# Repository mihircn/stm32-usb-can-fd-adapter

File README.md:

# STM32 USB-to-CAN FD Adapter

A USB-to-CAN adapter designed in KiCad around the STM32G0B1CBT6. It connects to a PC over USB and interfaces with a CAN bus through an external CAN transceiver.

## Features

- Micro-USB Type-B connection with USB Full-Speed
- STM32G0B1CBT6 microcontroller with USB and FDCAN peripherals
- TCAN332GD 3.3 V CAN transceiver
- USB ESD protection using USBLC6-2SC6
- CAN bus protection using NUP2105L
- AP2112K-3.3 regulator for the 3.3 V supply
- Jumper-selectable 120 Ω CAN termination
- SWD programming and debugging header
- Power and status LEDs
- Two-layer PCB with bottom-layer ground copper

## Hardware

| Component | Part |
|---|---|
| Microcontroller | STM32G0B1CBT6 |
| CAN transceiver | TCAN332GD |
| USB ESD protection | USBLC6-2SC6 |
| CAN protection | NUP2105L |
| Voltage regulator | AP2112K-3.3 |
| Crystal | ECS-160-12-33B2Q-CES-TR, 16 MHz |
| USB connector | Micro-USB Type-B |
| CAN connector | 3-pin screw terminal |

## PCB Design

### 3D View

### PCB Layout

### Schematic

## Design Specifications

- **EDA:** KiCad
- **PCB layers:** 2
- **Target dimensions:** 50 × 40 mm
- **Logic voltage:** 3.3 V
- **USB:** Full-Speed device interface
- **CAN:** CAN / CAN FD-capable hardware interface
- **Isolation:** Non-isolated

USB compatibility and CAN FD performance depend on configuration and validation on physical hardware.

## Repository Contents

- `Hardware/` — KiCad schematic, PCB, and project files
- `Manufacturing/gerbers/` — Gerber fabrication files
- `Manufacturing/drill/` — drill file
- `Docs/` — PCB renders, layout image, and schematic image

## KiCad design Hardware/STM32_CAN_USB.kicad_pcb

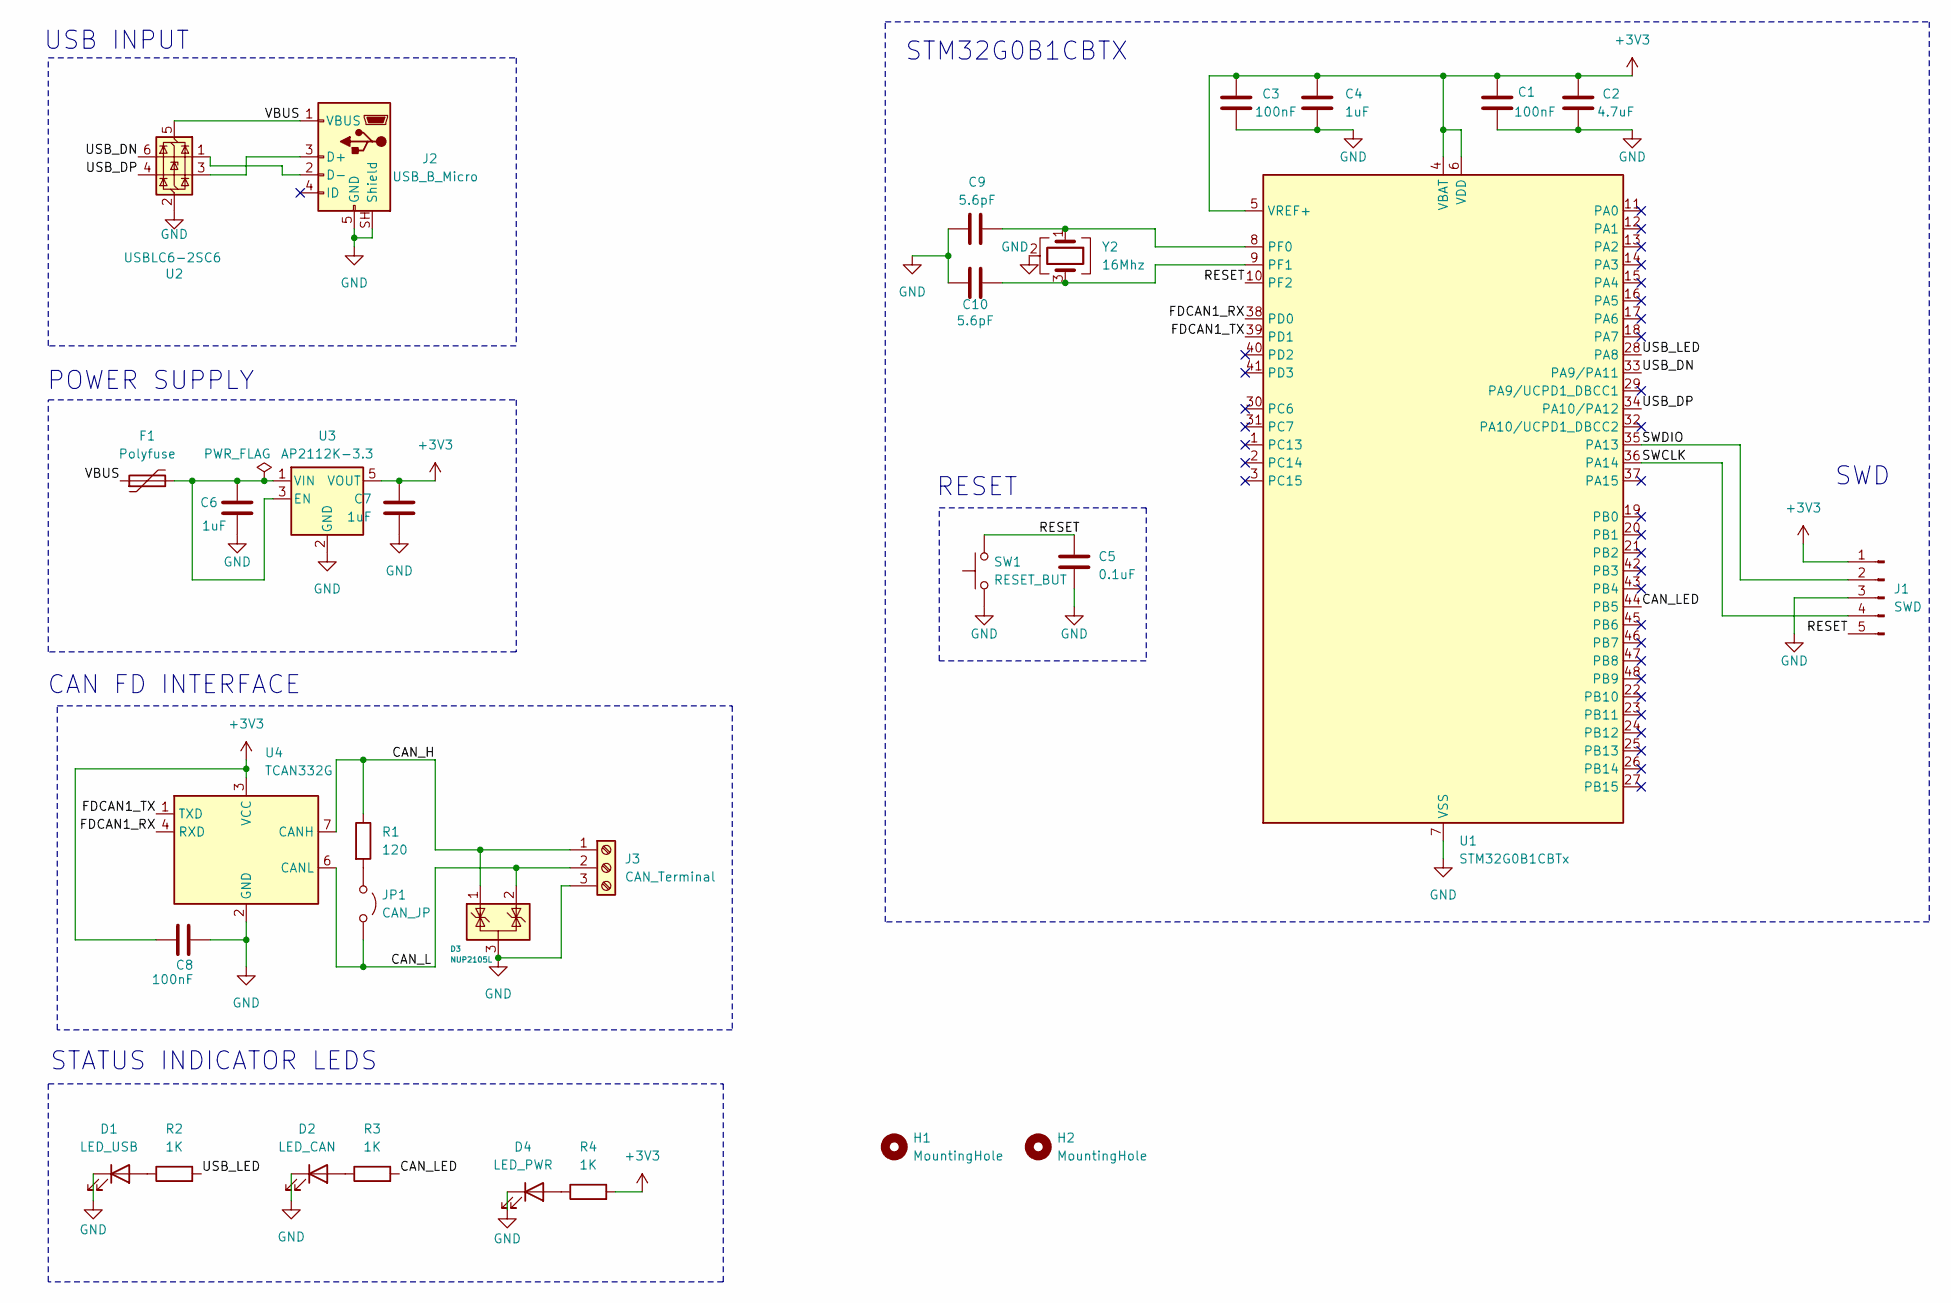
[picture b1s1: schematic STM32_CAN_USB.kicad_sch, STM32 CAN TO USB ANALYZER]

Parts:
C1, C3, C8: 100nF; C_0603_1608Metric
C2: 4.7uF; C_0805_2012Metric
C4, C6, C7: 1uF; C_0603_1608Metric
C5: 0.1uF; C_0603_1608Metric
C9, C10: 5.6pF; C_0603_1608Metric
D1: LED_USB; LED_0603_1608Metric
D2: LED_CAN; LED_0603_1608Metric
D3: NUP2105L; SOT-23
D4: LED_PWR; LED_0603_1608Metric
F1: Polyfuse; Fuse_1206_3216Metric
H1, H2: MountingHole; MountingHole_2mm
J1: SWD; PinHeader_1x05_P2.54mm_Vertical
J2: USB_B_Micro; USB_Micro-B_Amphenol_10118194_Horizontal
J3: CAN_Terminal; TerminalBlock_Phoenix_MKDS-1,5-3-5.08_1x03_P5.08mm_Horizont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
JP1: CAN_JP; PinHeader_1x02_P2.54mm_Vertical
R1: 120; R_0603_1608Metric
R2, R3, R4: 1K; R_0603_1608Metric
SW1: RESET_BUT; SW_Push_1P1T_NO_CK_KMR2
U1: STM32G0B1CBTx; LQFP-48_7x7mm_P0.5mm
U2: USBLC6-2SC6; SOT-23-6
U3: AP2112K-3.3; SOT-23-5
U4: TCAN332G; SOIC-8_3.9x4.9mm_P1.27mm
Y2: 16Mhz; Crystal_SMD_3225-4Pin_3.2x2.5mm

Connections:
+3V3: C1.1, C2.1, C3.1, C4.1, C7.1, C8.1, J1.1, R4.2, U1.4 (VBAT), U1.5 (VREF+), U1.6 (VDD), U3.5 (VOUT), U4.3 (VCC)
/CAN_H: D3.1 (K), J3.1, R1.1, U4.7 (CANH)
/CAN_L: D3.2 (K), J3.2, JP1.2 (B), U4.6 (CANL)
/CAN_LED: R3.2, U1.44 (PB5)
/FDCAN1_RX: U1.38 (PD0), U4.4 (RXD)
/FDCAN1_TX: U1.39 (PD1), U4.1 (TXD)
/RESET: C5.1, J1.5, SW1.2, U1.10 (PF2)
/SWCLK: J1.4, U1.36 (PA14)
/SWDIO: J1.2, U1.35 (PA13)
/USB_DN: U1.33 (PA9/PA11), U2.6 (I/O1)
/USB_DP: U1.34 (PA10/PA12), U2.4 (I/O2)
/USB_LED: R2.2, U1.28 (PA8)
/VBUS: F1.1, J2.1 (VBUS), U2.5 (VBUS)
GND: C1.2, C2.2, C3.2, C4.2, C5.2, C6.2, C7.2, C8.2, C9.2, C10.2, D1.1 (K), D2.1 (K), D3.3 (A), D4.1 (K), J1.3, J2.5 (GND), J2.SH (Shield), J3.3, SW1.1, U1.7 (VSS), U2.2 (GND), U3.2 (GND), U4.2 (GND), Y2.2 (G), Y2.4 (G)
unnamed: D1.2 (A), R2.1
unnamed: D2.2 (A), R3.1
unnamed: D4.2 (A), R4.1
unnamed: J2.3 (D+), U2.3 (I/O2)
unnamed: J2.2 (D-), U2.1 (I/O1)
unnamed: JP1.1 (A), R1.2
unnamed: C9.1, U1.8 (PF0), Y2.1
unnamed: C10.1, U1.9 (PF1), Y2.3
unnamed: C6.1, F1.2, U3.1 (VIN), U3.3 (EN)

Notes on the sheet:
STATUS INDICATOR LEDS
POWER SUPPLY
RESET
SWD
CAN FD INTERFACE
USB INPUT
STM32G0B1CBTX

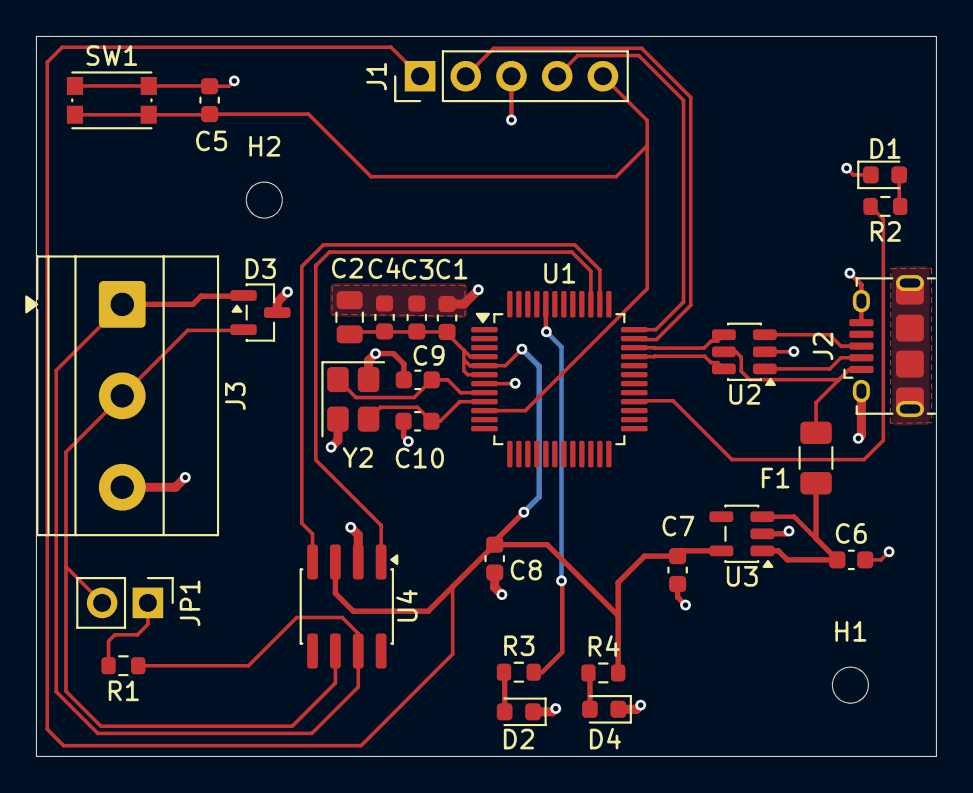
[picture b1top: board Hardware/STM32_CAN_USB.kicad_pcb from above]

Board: 2 copper layers, 50.0 x 40.0 mm, 31 parts (0 on the bottom side), 23 nets.

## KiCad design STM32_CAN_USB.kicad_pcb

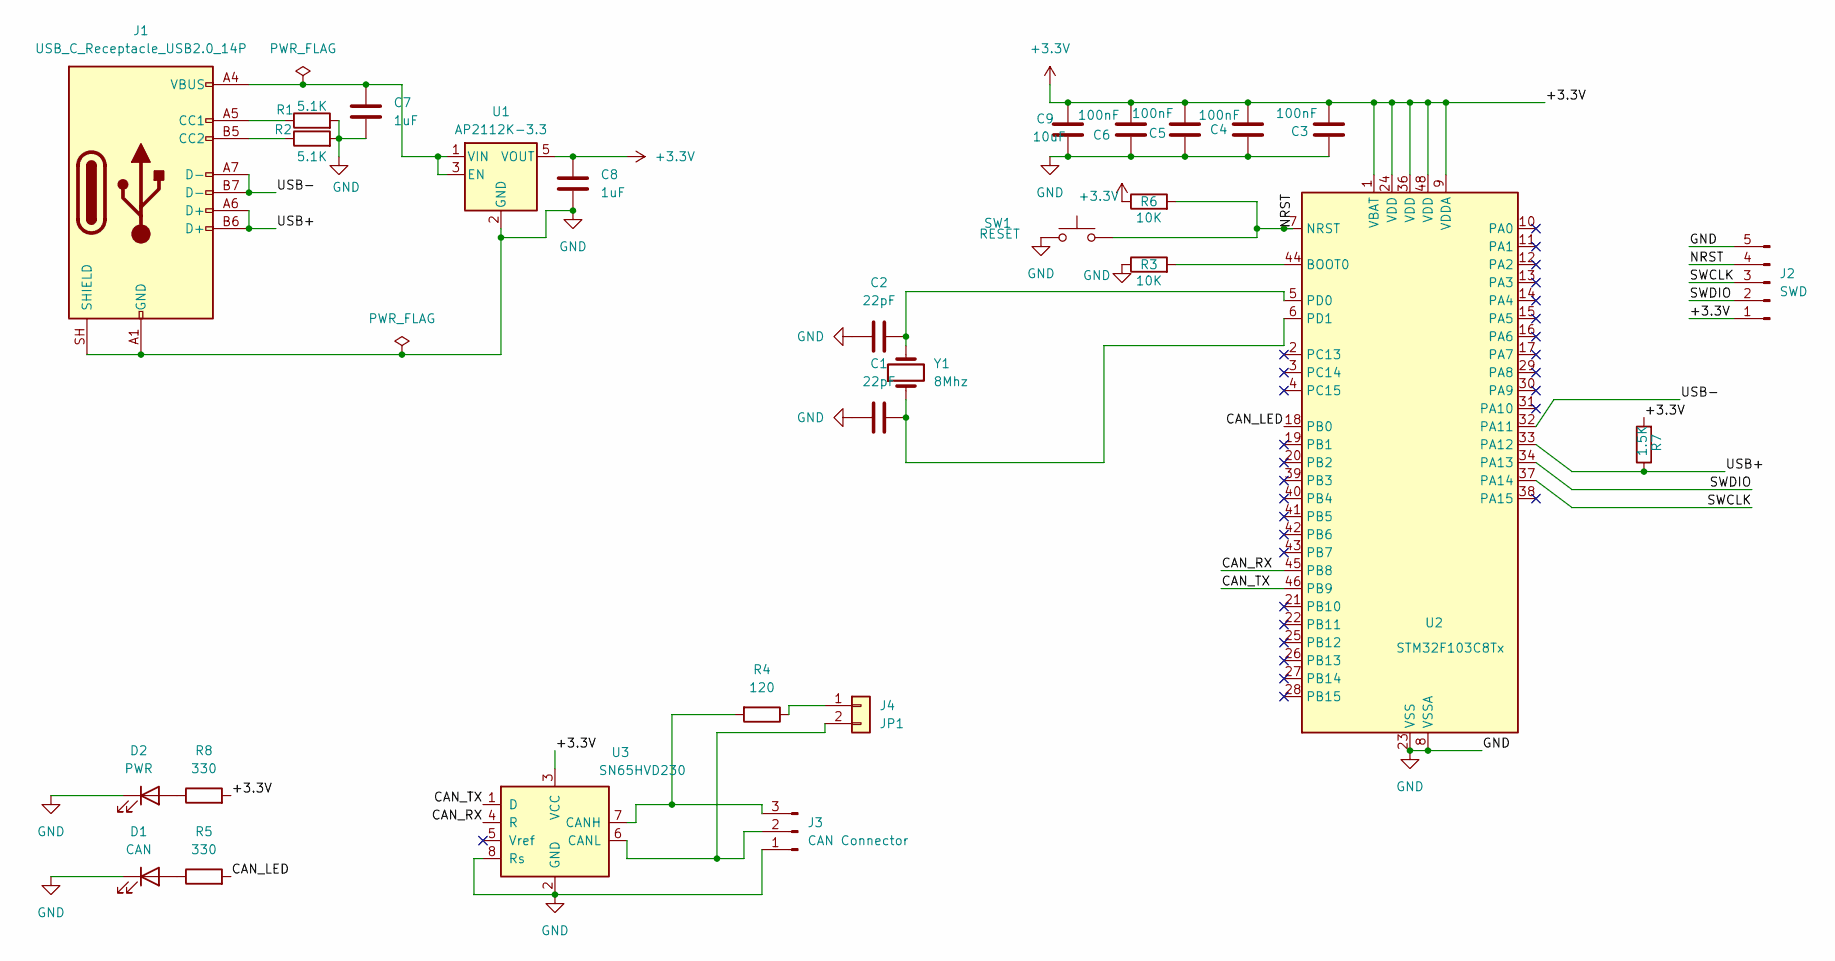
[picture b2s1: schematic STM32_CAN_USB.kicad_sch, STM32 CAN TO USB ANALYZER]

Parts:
C1, C2: 22pF; C_0603_1608Metric
C3, C4, C5, C6: 100nF; C_0603_1608Metric
C7, C8: 1uF; C_0603_1608Metric
C9: 10uF; C_0805_2012Metric
D1: CAN; LED_0805_2012Metric
D2: PWR; LED_0805_2012Metric
J1: USB_C_Receptacle_USB2.0_14P; USB_C_Receptacle_HRO_TYPE-C-31-M-12
J2: SWD; PinHeader_1x05_P2.54mm_Vertical
J3: CAN Connector; TerminalBlock_Phoenix_MKDS-1,5-3_1x03_P5.00mm_Horizontal
J4: JP1; PinHeader_1x02_P2.54mm_Vertical
R1, R2: 5.1K; R_0805_2012Metric
R3, R6: 10K; R_0805_2012Metric
R4: 120; R_0805_2012Metric
R5, R8: 330; R_0805_2012Metric
R7: 1.5K; R_0805_2012Metric
SW1: RESET; SW_SPST_TL3342
U1: AP2112K-3.3; SOT-23-5
U2: STM32F103C8Tx; LQFP-48_7x7mm_P0.5mm
U3: SN65HVD230; SOIC-8_3.9x4.9mm_P1.27mm
Y1: 8Mhz; Crystal_SMD_3225-4Pin_3.2x2.5mm

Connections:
+3.3V: C3.2, C4.2, C5.2, C6.2, C8.2, C9.1, J2.1, R6.1, R7.2, R8.2, U1.5 (VOUT), U2.1 (VBAT), U2.9 (VDDA), U2.24 (VDD), U2.36 (VDD), U2.48 (VDD), U3.3 (VCC)
/CAN_LED: R5.2, U2.18 (PB0)
/CAN_RX: U2.45 (PB8), U3.4 (R)
/CAN_TX: U2.46 (PB9), U3.1 (D)
/NRST: J2.4, R6.2, SW1.2, U2.7 (NRST)
/SWCLK: J2.3, U2.37 (PA14)
/SWDIO: J2.2, U2.34 (PA13)
/USB+: J1.A6 (D+), J1.B6 (D+), R7.1, U2.33 (PA12)
/USB-: J1.A7 (D-), J1.B7 (D-), U2.32 (PA11)
GND: C1.1, C2.2, C3.1, C4.1, C5.1, C6.1, C7.1, C8.1, C9.2, D1.1 (K), D2.1 (K), J1.A1 (GND), J1.A12 (GND), J1.B1 (GND), J1.B12 (GND), J1.SH (SHIELD), J2.5, J3.1, R1.2, R2.2, R3.1, SW1.1, U1.2 (GND), U2.8 (VSSA), U2.23 (VSS), U2.35 (VSS), U2.47 (VSS), U3.2 (GND), U3.8 (Rs)
unnamed: D1.2 (A), R5.1
unnamed: D2.2 (A), R8.1
unnamed: J1.A5 (CC1), R1.1
unnamed: J1.B5 (CC2), R2.1
unnamed: J3.2, J4.2, U3.6 (CANL)
unnamed: J3.3, R4.2, U3.7 (CANH)
unnamed: J4.1, R4.1
unnamed: C7.2, J1.A4 (VBUS), J1.A9 (VBUS), J1.B4 (VBUS), J1.B9 (VBUS), U1.1 (VIN), U1.3 (EN)
unnamed: R3.2, U2.44 (BOOT0)
unnamed: C2.1, U2.5 (PD0), Y1.2
unnamed: C1.2, U2.6 (PD1), Y1.1

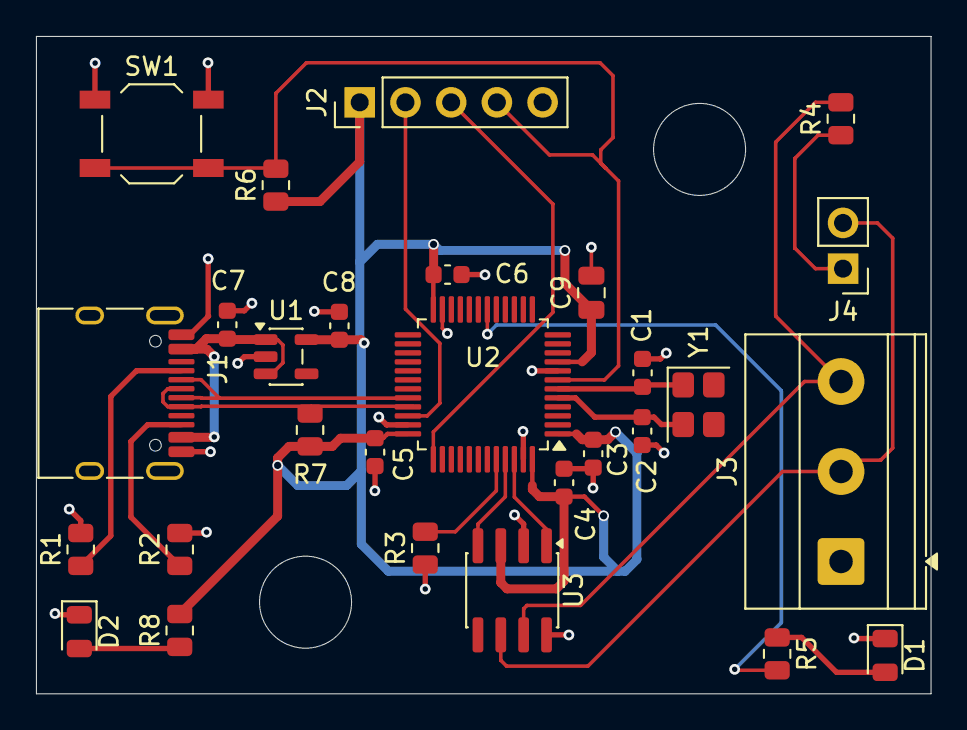
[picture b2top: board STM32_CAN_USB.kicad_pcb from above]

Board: 2 copper layers, 49.7 x 36.5 mm, 28 parts (0 on the bottom side), 21 nets.

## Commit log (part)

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2026-06-11 Add KiCad PCB files, renders, and documentation
2026-06-11 Update project README
